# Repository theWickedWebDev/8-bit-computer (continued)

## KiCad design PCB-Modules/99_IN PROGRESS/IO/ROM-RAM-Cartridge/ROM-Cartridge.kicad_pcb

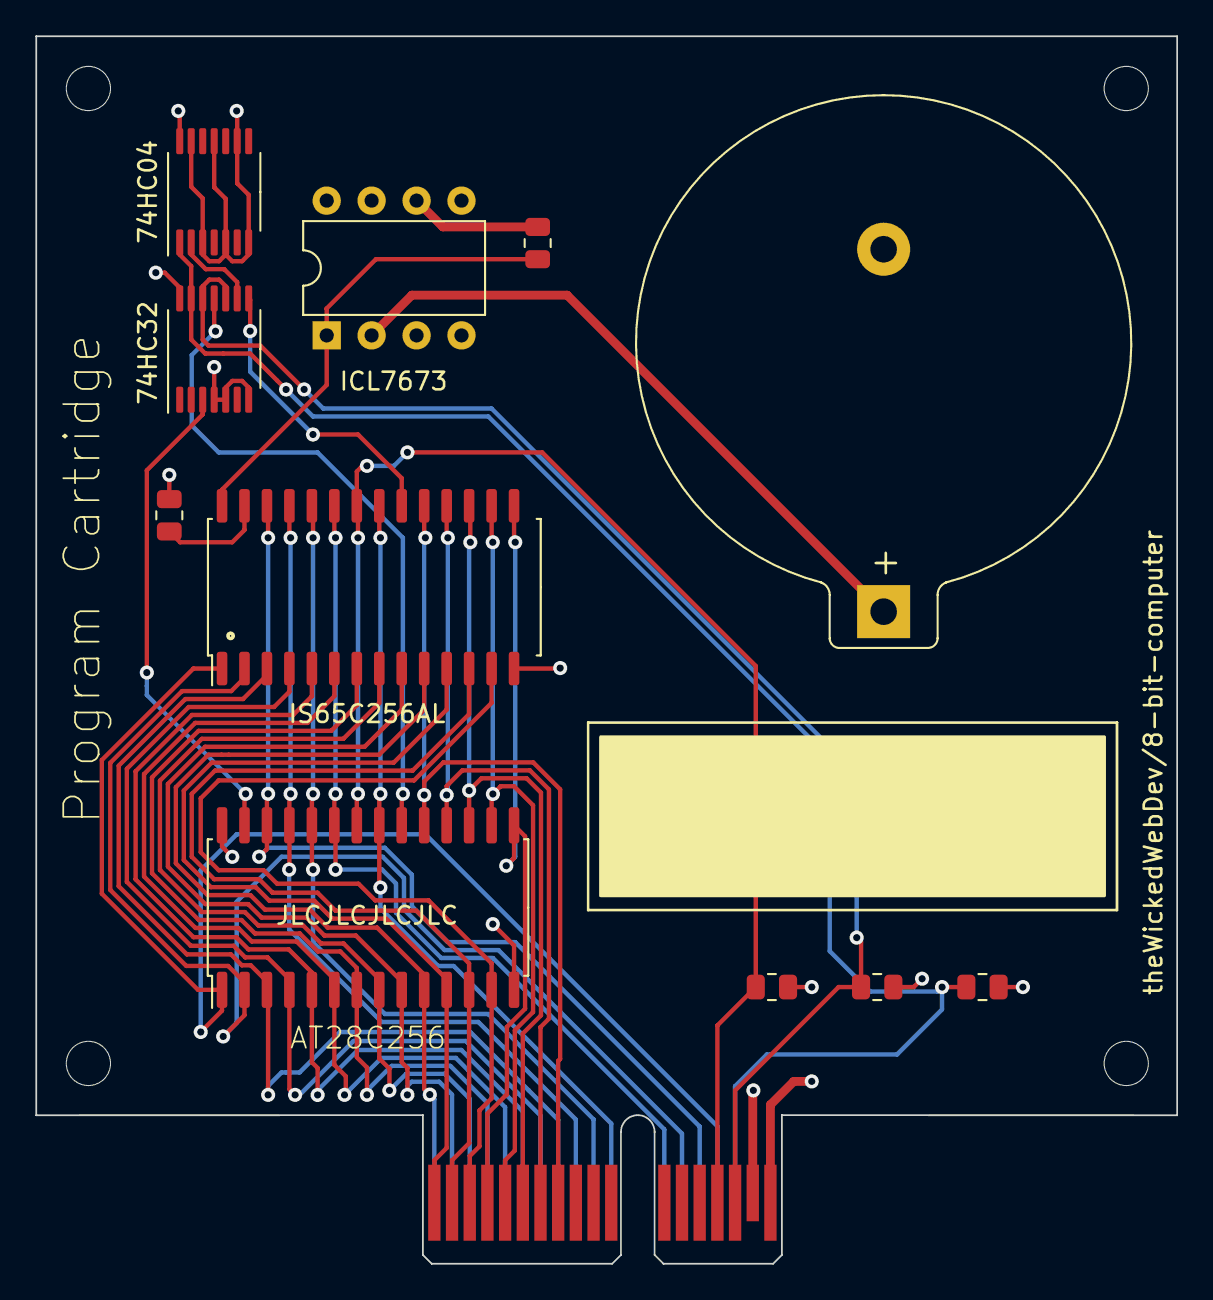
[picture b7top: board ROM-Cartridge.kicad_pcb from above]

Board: 4 copper layers, 64.5 x 69.4 mm, 12 parts (0 on the bottom side), 36 nets.

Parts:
BT1: Battery_Cell; BatteryHolder_Keystone_105_1x2430
J1: PCIE-036-02-X-D-RA; BUS_PCIexpress_x1
R1, R2, R3, R4, R5: R_Small_US; R_0805_2012Metric
U1: 28C256; SOIC-28W_7.5x17.9mm_P1.27mm
U3: ICL7673; DIP-8_W7.62mm
U4: 74LS04; TSSOP-14_4.4x5mm_P0.65mm
U5: IS65C256AL; SOP-28-RAM-ic
U6: 74LS32; TSSOP-14_4.4x5mm_P0.65mm

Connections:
+5V: J1.B18, U3.8 (Vp)
/A0: U1.10 (A0), U5.10 (A0)
/A1: U1.9 (A1), U5.9 (A1)
/A2: U1.8 (A2), U5.8 (A2)
/A3: U1.7 (A3), U5.7 (A3)
/A4: U1.6 (A4), U5.6 (A4)
/A5: U1.5 (A5), U5.5 (A5)
/A6: U1.4 (A6), U5.4 (A6)
/A7: U1.3 (A7), U5.3 (A7)
/A8: U1.25 (A8), U5.25 (A8)
/A9: J1.A10, U1.24 (A9), U5.24 (A9)
/A10: J1.A11, U1.21 (A10), U5.21 (A10)
/A11: J1.A12, U1.23 (A11), U5.23 (A11)
/A12: J1.A13, U1.2 (A12), U5.2 (A12)
/A13: J1.A14, U1.26 (A13), U5.26 (A13)
/A14: J1.A15, U1.1 (A14), U5.1 (A14)
/A15: J1.A16, R4.1, U4.1, U6.13
/D0: U1.11 (D0), U5.11 (D0)
/D1: U1.12 (D1), U5.12 (D1)
/D2: U1.13 (D2), U5.13 (D2)
/D3: U1.15 (D3), U5.15 (D3)
/D4: U1.16 (D4), U5.16 (D4)
/D5: U1.17 (D5), U5.17 (D5)
/D6: U1.18 (D6), U5.18 (D6)
/D7: U1.19 (D7), U5.19 (D7)
/~EN: J1.B16, R1.1, U6.10, U6.12
/~READ: J1.B15, R2.1, U1.22 (~OE), U5.22 (~OE)
/~ROM_WRITE: U1.27 (~WE), U6.3
/~WRITE: R3.1, U5.27 (~WE)
GND: BT1.2 (-), J1.B17, U1.14 (GND), U3.4 (Gnd), U4.3, U4.5, U4.7 (GND), U4.9, U4.11, U4.13, U5.14 (GND), U6.4, U6.5, U6.7 (GND)
unnamed: BT1.1 (+), U3.2 (Vs)
unnamed: R5.2, U3.6 (PBar)
unnamed: U1.20 (~CS), U6.11
unnamed: U4.2, U6.9
unnamed: U5.20 (~CS), U6.8
VCC: R1.2, R2.2, R3.2, R4.2, R5.1, U1.28 (VCC), U3.1 (VO), U4.14 (VCC), U5.28 (VCC), U6.14 (VCC)

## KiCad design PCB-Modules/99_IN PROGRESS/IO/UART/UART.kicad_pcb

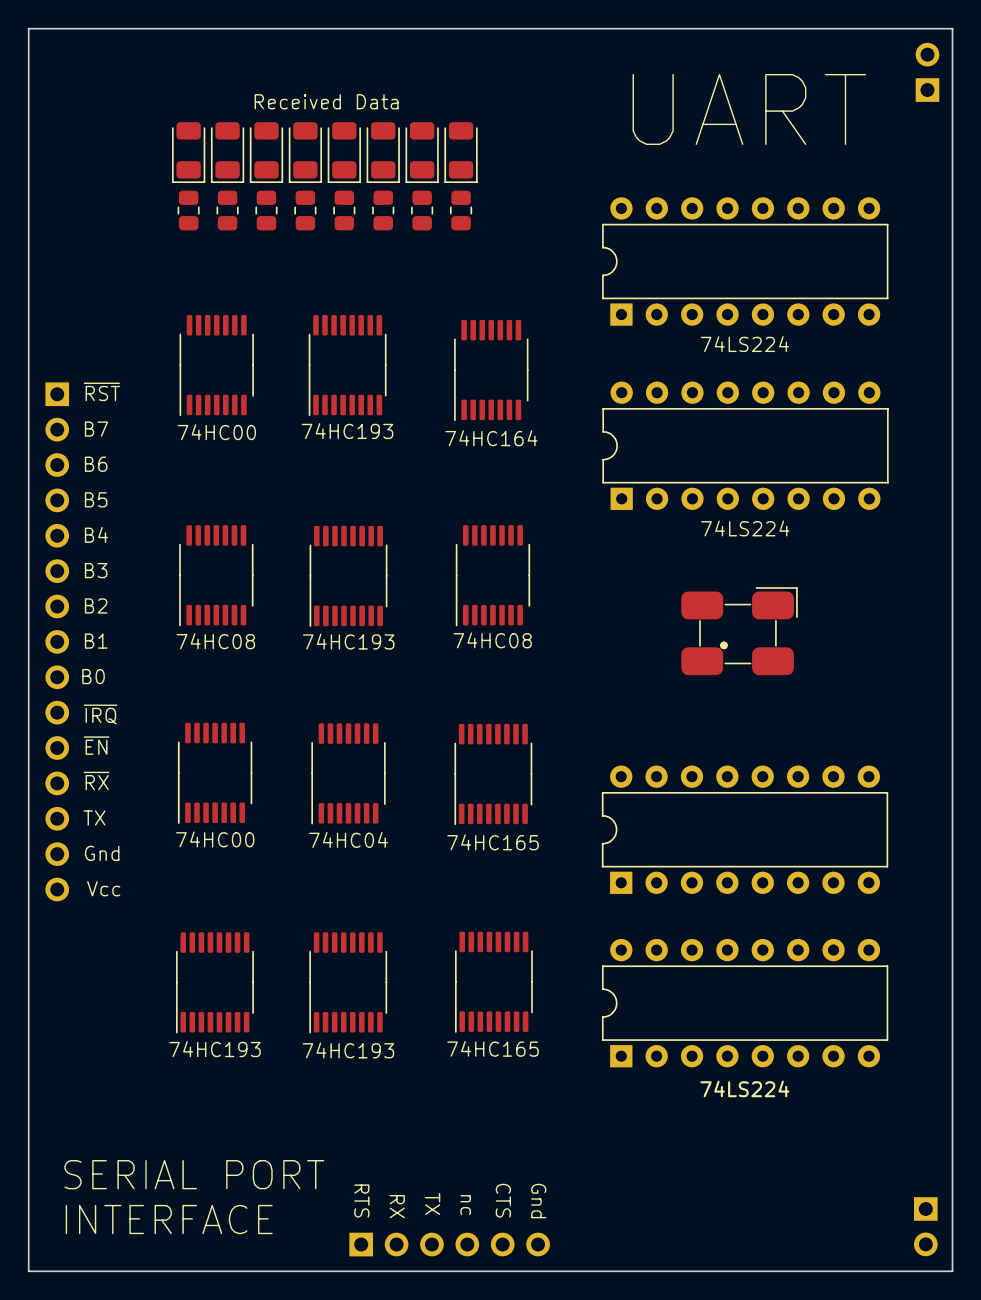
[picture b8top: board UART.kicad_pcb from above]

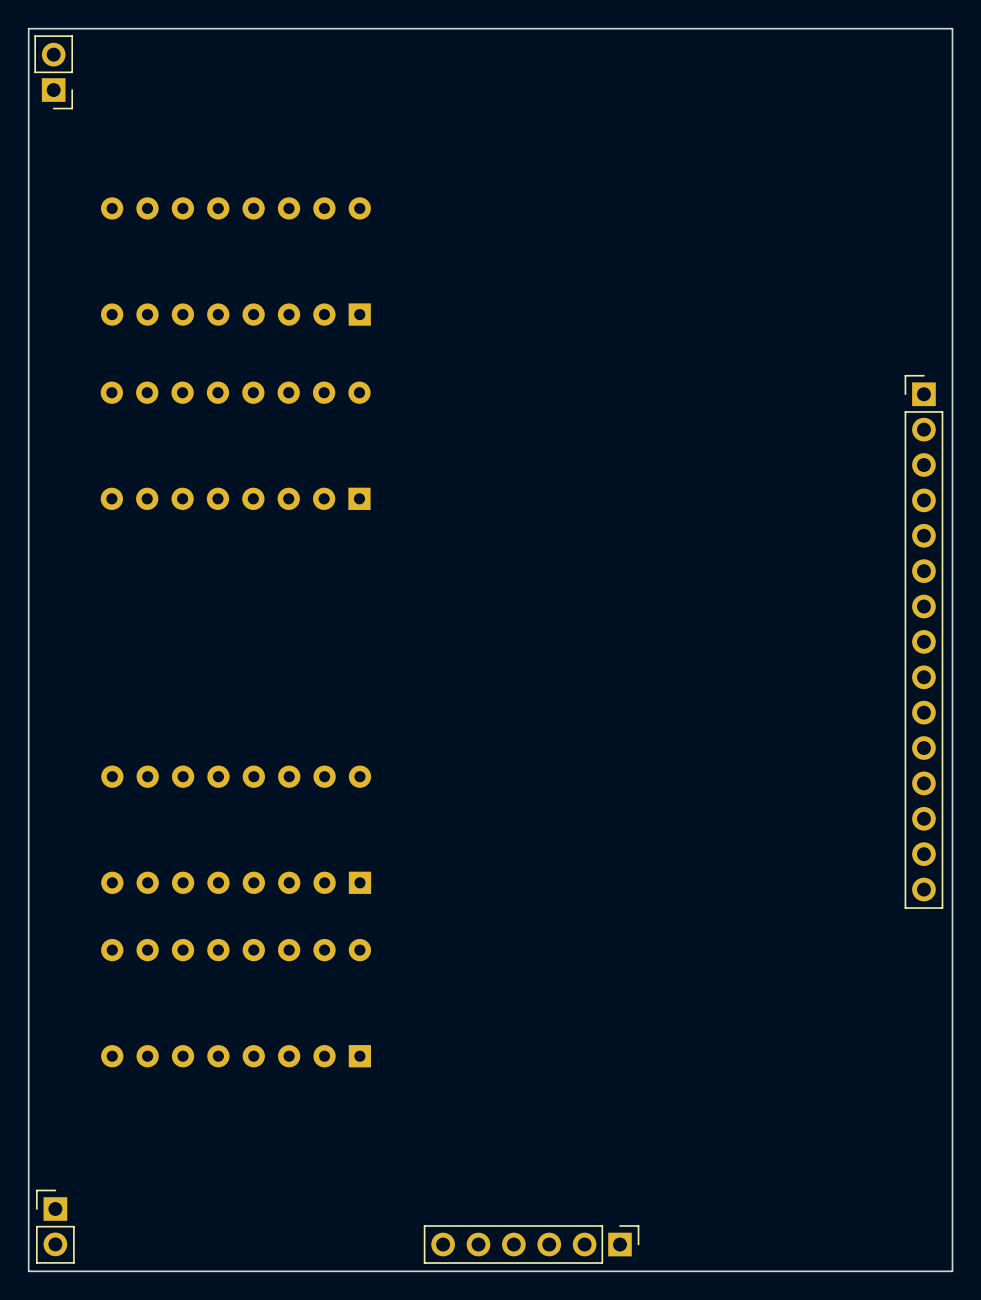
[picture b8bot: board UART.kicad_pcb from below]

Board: 4 copper layers, 66.3 x 89.2 mm, 37 parts (4 on the bottom side), 66 nets, no tracks yet.

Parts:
D1, D2, D3, D4, D5, D6, D7, D8: LED; LED_1206_3216Metric
J1: Conn_01x06; PinHeader_1x06_P2.54mm_Vertical
J2: Conn_01x15; PinHeader_1x15_P2.54mm_Vertical
J3, J4: Conn_01x02; PinHeader_1x02_P2.54mm_Vertical
R1, R2, R3, R4, R5, R6, R7, R8: 1kohm; R_0805_2012Metric
U1, U2, U3, U4: 74LS193; TSSOP-16_4.4x5mm_P0.65mm
U5, U14: 74LS08; TSSOP-14_4.4x5mm_P0.65mm
U6, U7: 74LS00; TSSOP-14_4.4x5mm_P0.65mm
U8: 74LS04; TSSOP-14_4.4x5mm_P0.65mm
U9: 74HC164; TSSOP-14_4.4x5mm_P0.65mm
U10, U11: 74LS165; TSSOP-16_4.4x5mm_P0.65mm
U12, U13, U15, U18: 74LS224; DIP-16_W7.62mm
Y1: Crystal_GND24; CFPS-72 SMD Clock

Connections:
/READ: U12.1 (OE), U12.15 (UNCK), U13.1 (OE), U13.15 (UNCK), U14.3
/TX0: D8.2 (A), U9.3 (Q0), U12.4 (D0)
/TX1: D7.2 (A), U9.4 (Q1), U12.5 (D1)
/TX2: D6.2 (A), U9.5 (Q2), U12.6 (D2)
/TX3: D5.2 (A), U9.6 (Q3), U12.7 (D3)
/TX4: D4.2 (A), U9.10 (Q4), U13.4 (D0)
/TX5: D3.2 (A), U9.11 (Q5), U13.5 (D1)
/TX6: D2.2 (A), U9.12 (Q6), U13.6 (D2)
/TX7: D1.2 (A), U9.13 (Q7), U13.7 (D3)
/TX_CLOCK: U2.7 (QD), U4.5 (UP), U6.10, U10.2 (CP), U11.2 (CP)
/TX_START: U4.11 (~LOAD), U6.3, U6.5, U10.1 (~PL), U11.1 (~PL), U15.1 (OE), U15.15 (UNCK), U18.1 (OE), U18.15 (UNCK)
/WRITE: U3.14 (CLR), U7.3, U7.4, U12.3 (LDCK), U13.3 (LDCK)
BUS0: J2.2, U12.13 (Q0), U15.4 (D0)
BUS1: J2.3, U12.12 (Q1), U15.5 (D1)
BUS2: J2.4, U12.11 (Q2), U15.6 (D2)
BUS3: J2.5, U12.10 (Q3), U15.7 (D3)
BUS4: J2.6, U13.13 (Q0), U18.4 (D0)
BUS5: J2.7, U13.12 (Q1), U18.5 (D1)
BUS6: J2.8, U13.11 (Q2), U18.6 (D2)
BUS7: J2.9, U13.10 (Q3), U18.7 (D3)
EN: U5.2, U8.6, U14.1
GND: J1.6, J2.14, R1.2, R2.2, R3.2, R4.2, R5.2, R6.2, R7.2, R8.2, U1.1 (B), U1.8 (GND), U1.10 (C), U1.14 (CLR), U2.1 (B), U2.8 (GND), U2.9 (D), U2.10 (C), U2.14 (CLR), U2.15 (A), U3.1 (B), U3.8 (GND), U3.9 (D), U3.10 (C), U3.15 (A), U4.1 (B), U4.8 (GND), U4.9 (D), U4.14 (CLR), U5.7 (GND), U5.12, U5.13, U6.7 (GND), U6.12, U6.13, U7.7 (GND), U7.9, U7.10, U7.12, U7.13, U8.7 (GND), U8.13, U9.7 (GND), U10.5 (D6), U10.8 (GND), U10.15 (~CE), U11.8 (GND), U11.15 (~CE), U12.8 (GND), U13.8 (GND), U14.7 (GND), U14.12, U14.13, U15.8 (GND), U18.8 (GND), Y1.2
unnamed: D1.1 (K), R1.1
unnamed: D2.1 (K), R2.1
unnamed: D3.1 (K), R3.1
unnamed: D4.1 (K), R4.1
unnamed: D5.1 (K), R5.1
unnamed: D6.1 (K), R6.1
unnamed: D7.1 (K), R7.1
unnamed: D8.1 (K), R8.1
unnamed: U1.4 (DOWN), U3.7 (QD), U9.8 (CP)
unnamed: U1.11 (~LOAD), U7.2, U7.6
unnamed: U1.13 (~BO), U7.1
unnamed: U4.12 (~CO), U6.4
unnamed: U5.5, U18.2 (IR)
unnamed: U5.8, U8.11
unnamed: U6.2, U6.8
unnamed: U8.1, U14.8
unnamed: U10.10 (DS), U11.9 (Q7)
unnamed: U12.2 (IR), U14.4
unnamed: U12.14 (OR), U14.9
unnamed: U13.2 (IR), U14.5
unnamed: U13.14 (OR), U14.10
unnamed: U5.4, U15.2 (IR)
unnamed: U5.9, U15.14 (OR)
unnamed: U5.10, U18.14 (OR)
RECEIVE_BYTE: J2.12, U8.4, U14.2
RX0: U10.4 (D5), U15.13 (Q0)
RX1: U10.3 (D4), U15.12 (Q1)
RX2: U10.14 (D3), U15.11 (Q2)
RX3: U10.13 (D2), U15.10 (Q3)
RX4: U10.12 (D1), U18.13 (Q0)
RX5: U10.11 (D0), U18.12 (Q1)
RX6: U11.6 (D7), U18.11 (Q2)
RX7: U11.5 (D6), U18.10 (Q3)
SER_CTS: J1.5, U14.6
SER_RTS: J1.1, U6.9, U8.10
SER_RX: J1.2, U10.9 (Q7)
SER_TX: J1.3, U7.5, U9.1 (DSA)
TF_DATA_READ: U6.1, U6.6
TRANSMIT_BYTE: J2.13, U5.1, U5.3, U8.8, U15.3 (LDCK), U18.3 (LDCK)
UART_CLOCK: U2.5 (UP), U3.5 (UP), Y1.3
VCC: J2.15, U1.5 (UP), U1.9 (D), U1.15 (A), U1.16 (VCC), U2.4 (DOWN), U2.11 (~LOAD), U2.16 (VCC), U3.4 (DOWN), U3.11 (~LOAD), U3.16 (VCC), U4.4 (DOWN), U4.10 (C), U4.15 (A), U4.16 (VCC), U5.14 (VCC), U6.14 (VCC), U7.14 (VCC), U8.14 (VCC), U9.2 (DSB), U9.9 (~MR), U9.14 (VCC), U10.6 (D7), U10.16 (VCC), U11.3 (D4), U11.4 (D5), U11.10 (DS), U11.11 (D0), U11.12 (D1), U11.13 (D2), U11.14 (D3), U11.16 (VCC), U12.16 (VCC), U13.16 (VCC), U14.14 (VCC), U15.16 (VCC), U18.16 (VCC), Y1.4
~EN: J2.11, U8.5
~RESET_BUFFERS: J2.1, U12.9 (~CLR), U13.9 (~CLR), U15.9 (~CLR), U18.9 (~CLR)
~RX_IRQ: J2.10, U8.2
